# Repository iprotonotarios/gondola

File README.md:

# gondola
A parametric robot infrastructure for repeatable mobile experiments

http://arxiv.org/abs/1601.07457

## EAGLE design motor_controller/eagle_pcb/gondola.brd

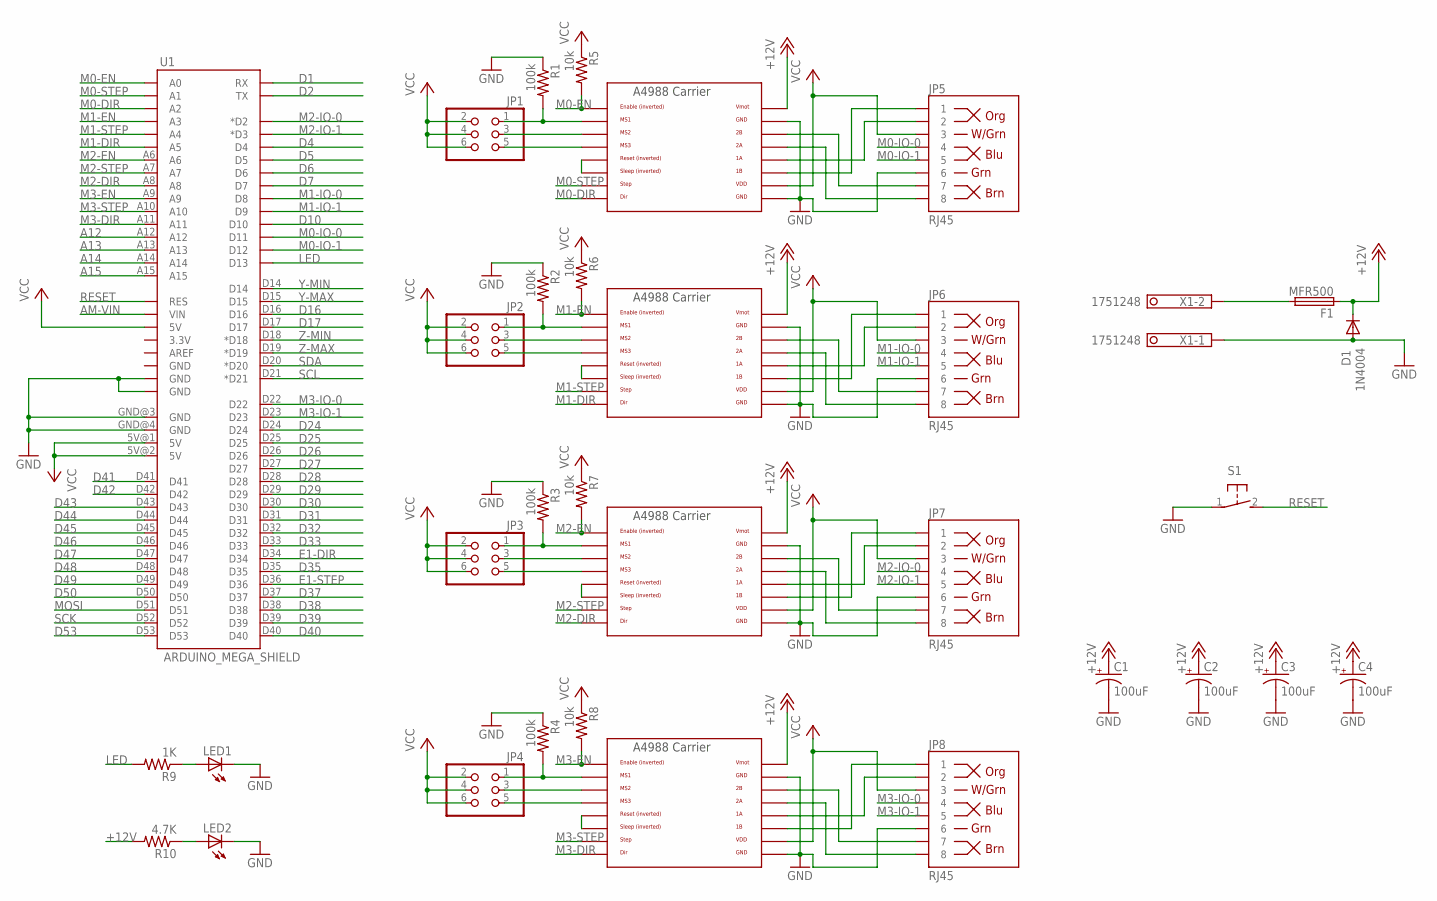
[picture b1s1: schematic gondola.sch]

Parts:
C1, C2, C3, C4: 100uF; 153CLV-0605
D1: 1N4004; DO41-10
F1: MFR500
JP1, JP2, JP3, JP4: PINHD-2X3; 2X03
JP5, JP6, JP7, JP8: RJ45; RJ45-8
LED1, LED2: LEDCHIP-LED0805; CHIP-LED0805
R1, R2, R3, R4: 100k; R0805
R5, R6, R7, R8: 10k; R0805
R9: 1K; R0805
R10: 4.7K; R0805
S1: 31-XX; B3F-31XX
U1: ARDUINO_MEGA_SHIELD
U$1, U$2, U$3, U$4: A4988BREAKOUT
X1: 1751248

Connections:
+12V: C1.+, C2.+, C3.+, C4.+, D1.C, F1.1, R10.2, U$1.VMOT, U$2.VMOT, U$3.VMOT, U$4.VMOT
A12: U1.A12
A13: U1.A13
A14: U1.A14
A15: U1.A15
AM-VIN: U1.VIN
D1: U1.RX
D2: U1.TX
D4: U1.D4
D5: U1.D5
D6: U1.D6
D7: U1.D7
D10: U1.D10
D16: U1.D16
D17: U1.D17
D24: U1.D24
D25: U1.D25
D26: U1.D26
D27: U1.D27
D28: U1.D28
D29: U1.D29
D30: U1.D30
D31: U1.D31
D32: U1.D32
D33: U1.D33
D35: U1.D35
D37: U1.D37
D38: U1.D38
D39: U1.D39
D40: U1.D40
D41: U1.D41
D42: U1.D42
D43: U1.D43
D44: U1.D44
D45: U1.D45
D46: U1.D46
D47: U1.D47
D48: U1.D48
D49: U1.D49
D50: U1.D50
D53: U1.D53
E1-DIR: U1.D34
E1-STEP: U1.D36
GND: C1.-, C2.-, C3.-, C4.-, D1.A, JP5.6, JP6.6, JP7.6, JP8.6, LED1.C, LED2.C, R1.1, R2.1, R3.1, R4.1, S1.1, U1.GND@0 (GND), U1.GND@1 (GND), U1.GND@3 (GND), U1.GND@4 (GND), U$1.GND, U$1.GND@0 (GND), U$2.GND, U$2.GND@0 (GND), U$3.GND, U$3.GND@0 (GND), U$4.GND, U$4.GND@0 (GND), X1.1
LED: R9.2, U1.D13
M0-DIR: U1.A2, U$4.DIR
M0-EN: R5.2, U1.A0, U$4.EN
M0-IO-0: JP5.4, U1.D11
M0-IO-1: JP5.5, U1.D12
M0-STEP: U1.A1, U$4.STEP
M1-DIR: U1.A5, U$1.DIR
M1-EN: R6.2, U1.A3, U$1.EN
M1-IO-0: JP6.4, U1.D8
M1-IO-1: JP6.5, U1.D9
M1-STEP: U1.A4, U$1.STEP
M2-DIR: U1.A8, U$2.DIR
M2-EN: R7.2, U1.A6, U$2.EN
M2-IO-0: JP7.4, U1.D2 (*D2)
M2-IO-1: JP7.5, U1.D3 (*D3)
M2-STEP: U1.A7, U$2.STEP
M3-DIR: U1.A11, U$3.DIR
M3-EN: R8.2, U1.A9, U$3.EN
M3-IO-0: JP8.4, U1.D22
M3-IO-1: JP8.5, U1.D23
M3-STEP: U1.A10, U$3.STEP
MOSI: U1.D51
unnamed: JP2.5, U$1.MS3
unnamed: U$1.RST, U$1.SLP (SLEEP)
unnamed: JP1.5, U$4.MS3
unnamed: U$4.RST, U$4.SLP (SLEEP)
unnamed: JP1.1, R1.2, U$4.MS1
unnamed: JP1.3, U$4.MS2
unnamed: JP2.1, R2.2, U$1.MS1
unnamed: JP6.7, U$1.2B
unnamed: JP6.8, U$1.2A
unnamed: JP6.1, U$1.1B
unnamed: JP6.2, U$1.1A
unnamed: JP2.3, U$1.MS2
unnamed: JP5.7, U$4.2B
unnamed: JP5.8, U$4.2A
unnamed: JP5.1, U$4.1B
unnamed: JP5.2, U$4.1A
unnamed: JP3.5, U$2.MS3
unnamed: U$2.RST, U$2.SLP (SLEEP)
unnamed: JP3.1, R3.2, U$2.MS1
unnamed: JP3.3, U$2.MS2
unnamed: JP7.7, U$2.2B
unnamed: JP7.8, U$2.2A
unnamed: JP7.1, U$2.1B
unnamed: JP7.2, U$2.1A
unnamed: JP4.5, U$3.MS3
unnamed: U$3.RST, U$3.SLP (SLEEP)
unnamed: JP4.1, R4.2, U$3.MS1
unnamed: JP4.3, U$3.MS2
unnamed: JP8.7, U$3.2B
unnamed: JP8.8, U$3.2A
unnamed: JP8.2, U$3.1A
unnamed: JP8.1, U$3.1B
unnamed: LED2.A, R10.1
unnamed: LED1.A, R9.1
unnamed: F1.2, X1.2
RESET: S1.2 (S), U1.RES
SCK: U1.D52
SCL: U1.D21 (*D21)
SDA: U1.D20 (*D20)
VCC: JP1.2, JP1.4, JP1.6, JP2.2, JP2.4, JP2.6, JP3.2, JP3.4, JP3.6, JP4.2, JP4.4, JP4.6, JP5.3, JP6.3, JP7.3, JP8.3, R5.1, R6.1, R7.1, R8.1, U1.5V@0 (5V), U1.5V@1 (5V), U1.5V@2 (5V), U$1.VDD, U$2.VDD, U$3.VDD, U$4.VDD
Y-MAX: U1.D15
Y-MIN: U1.D14
Z-MAX: U1.D19 (*D19)
Z-MIN: U1.D18 (*D18)

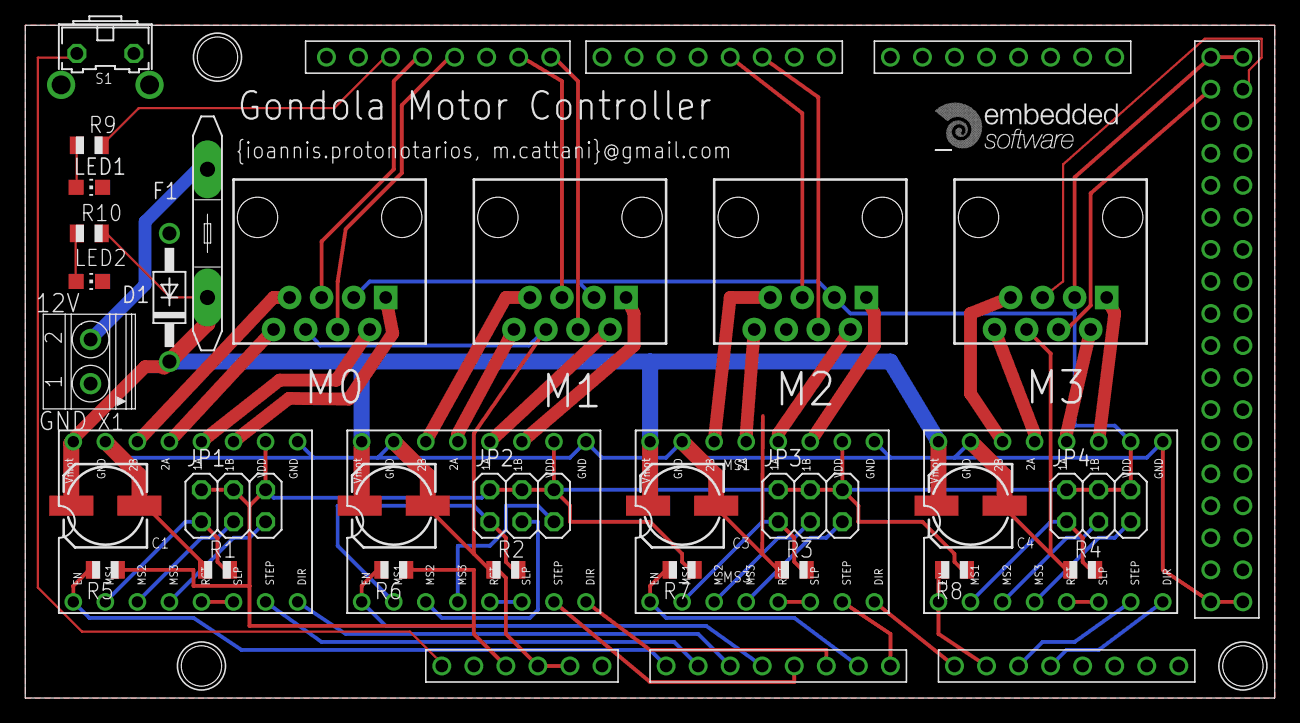
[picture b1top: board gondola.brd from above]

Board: 2 copper layers, 99.0 x 53.3 mm, 33 parts (0 on the bottom side), 60 nets.

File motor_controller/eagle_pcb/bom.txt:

Part Value               Device              Package             Description                          MF MPN      OC_FARNELL OC_NEWARK PROD_ID    VALUE
C1   100uF               CPOL-US153CLV-0605  153CLV-0605         POLARIZED CAPACITOR, American symbol                                                  
C2   100uF               CPOL-US153CLV-0605  153CLV-0605         POLARIZED CAPACITOR, American symbol                                                  
C3   100uF               CPOL-US153CLV-0605  153CLV-0605         POLARIZED CAPACITOR, American symbol                                                  
C4   100uF               CPOL-US153CLV-0605  153CLV-0605         POLARIZED CAPACITOR, American symbol                                                  
D1   1N4004              1N4004              DO41-10             DIODE                                                                                 
F1   MFR500              PTCFUSE             MFR500              LITTLEFUSE                                                                            
JP1                      PINHD-2X3           2X03                PIN HEADER                                                                            
JP2                      PINHD-2X3           2X03                PIN HEADER                                                                            
JP3                      PINHD-2X3           2X03                PIN HEADER                                                                            
JP4                      PINHD-2X3           2X03                PIN HEADER                                                                            
JP5  RJ45                RJ45-8PTH           RJ45-8              RJ45 Jack                                                             CONN-08506 RJ45 
JP6  RJ45                RJ45-8PTH           RJ45-8              RJ45 Jack                                                             CONN-08506 RJ45 
JP7  RJ45                RJ45-8PTH           RJ45-8              RJ45 Jack                                                             CONN-08506 RJ45 
JP8  RJ45                RJ45-8PTH           RJ45-8              RJ45 Jack                                                             CONN-08506 RJ45 
LED1                     LEDCHIP-LED0805     CHIP-LED0805        LED                                                                                   
LED2                     LEDCHIP-LED0805     CHIP-LED0805        LED                                                                                   
R1   100k                R-US_R0805          R0805               RESISTOR, American symbol                                                             
R2   100k                R-US_R0805          R0805               RESISTOR, American symbol                                                             
R3   100k                R-US_R0805          R0805               RESISTOR, American symbol                                                             
R4   100k                R-US_R0805          R0805               RESISTOR, American symbol                                                             
R5   10k                 R-US_R0805          R0805               RESISTOR, American symbol                                                             
R6   10k                 R-US_R0805          R0805               RESISTOR, American symbol                                                             
R7   10k                 R-US_R0805          R0805               RESISTOR, American symbol                                                             
R8   10k                 R-US_R0805          R0805               RESISTOR, American symbol                                                             
R9   1K                  R-US_R0805          R0805               RESISTOR, American symbol                                                             
R10  4.7K                R-US_R0805          R0805               RESISTOR, American symbol                                                             
S1                       31-XX               B3F-31XX            OMRON SWITCH                            B3F-3100 959704     36M3582                   
U$1  A4988BREAKOUT       A4988BREAKOUT       A4988BREAKOUT                                                                                             
U$2  A4988BREAKOUT       A4988BREAKOUT       A4988BREAKOUT                                                                                             
U$3  A4988BREAKOUT       A4988BREAKOUT       A4988BREAKOUT                                                                                             
U$4  A4988BREAKOUT       A4988BREAKOUT       A4988BREAKOUT                                                                                             
U1   ARDUINO_MEGA_SHIELD ARDUINO_MEGA_SHIELD ARDUINO_MEGA_SHIELD                                                                                       
X1   1751248             1751248             1751248             MKDS 1/ 2-3,5 Printklemme                        unknown    unknown

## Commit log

2016-01-28 added 3d-printed parts
2016-08-30 new motor controller
2016-08-30 added system controller
2016-08-30 removed old controller
2016-08-30 removed old files
2016-08-30 fixed comments
2016-09-08 liner motion arduino
    added linear motion to arduino
2016-09-09 smooth movement + sensing part (still no parsing from serial)
2016-10-07 complete smooth engine motors
2016-10-07 Fixed floating point movement
2016-10-14 added heatmap plotting
2016-10-17 last changes
2017-06-07 fixed bug
2017-07-10 added Arduino stand-alone version of gondola
2017-07-10 added readme
2017-07-10 fixed initial spooling distance
2017-07-10 moved config and definitions to different files
2017-07-17 added output whenever gondola reach its position
2017-07-17 added config file for wemos D1 mini

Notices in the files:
parts and their libraries:
SparkFun-Connectors: Licensing: Creative Commons ShareAlike 4.0 International - https://creativecommons.org/licenses/by-sa/4.0
